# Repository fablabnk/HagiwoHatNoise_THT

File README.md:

# HagiwoHatNoise

# Notes

5v from Arduino or directly from 5V rail?
Patch submodule uses 22uF ceramic decoupling cap instead of 10uF electrolytic

# ToDo

- move decoupling caps close to Arduino on layout (both?!)

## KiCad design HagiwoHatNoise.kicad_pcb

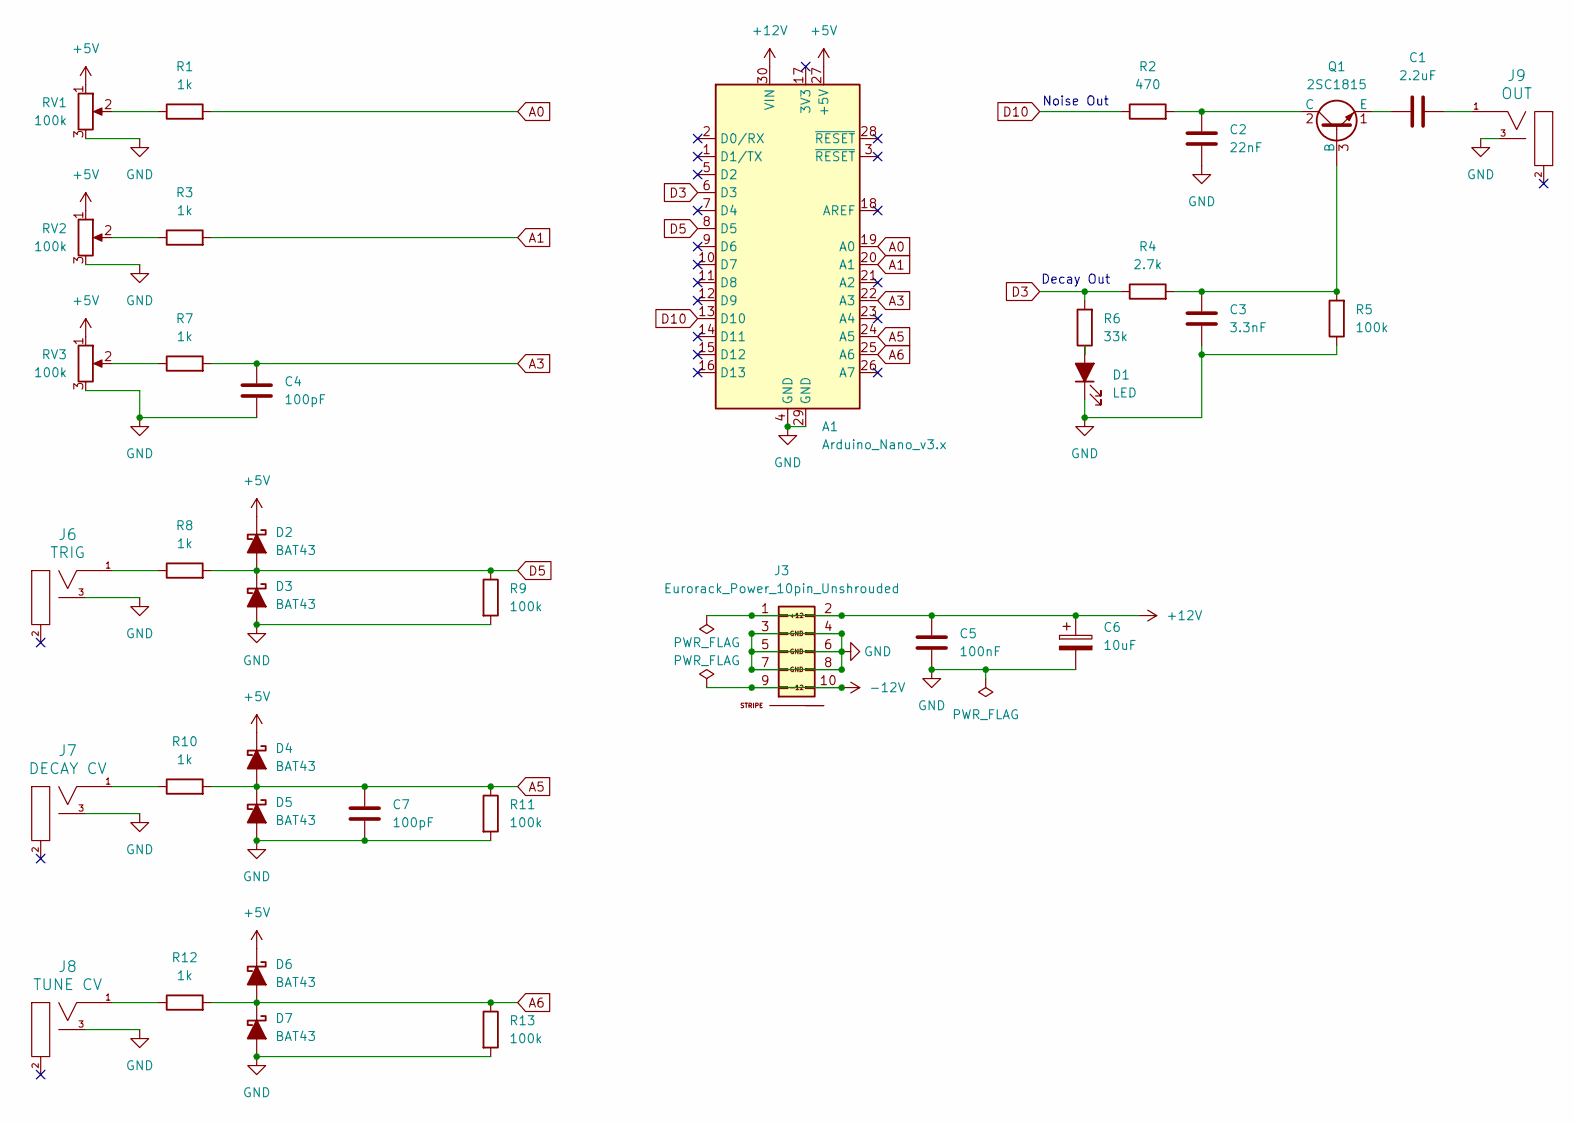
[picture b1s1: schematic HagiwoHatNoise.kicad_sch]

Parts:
A1: Arduino_Nano_v3.x; Arduino_Nano
C1: 2.2uF; C_Disc_D3.8mm_W2.6mm_P2.50mm
C2: 22nF; C_Disc_D3.8mm_W2.6mm_P2.50mm
C3: 3.3nF; C_Disc_D3.8mm_W2.6mm_P2.50mm
C4, C7: 100pF; C_Disc_D3.8mm_W2.6mm_P2.50mm
C5: 100nF; C_Disc_D3.8mm_W2.6mm_P2.50mm
C6: 10uF; CP_Radial_D4.0mm_P1.50mm
D1: LED; LED_D5.0mm
D2, D3, D4, D5, D6, D7: BAT43; D_DO-35_SOD27_P7.62mm_Horizontal_Widened_No_K
J3: Eurorack_Power_10pin_Unshrouded; IDC-Header_2x05_P2.54mm_Vertical_Euro_Power_Striped_Thicker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; Part Number 1-1002FBV0T
J6: TRIG; EighthInch_PJ398SM_3mmNPTH; Part Number WQP-WQP518MA
J7: DECAY CV; EighthInch_PJ398SM_3mmNPTH; Part Number WQP-WQP518MA
J8: TUNE CV; EighthInch_PJ398SM_3mmNPTH; Part Number WQP-WQP518MA
J9: OUT; EighthInch_PJ398SM_3mmNPTH; Part Number WQP-WQP518MA
Q1: 2SC1815; TO-92_Inline
R1, R3, R7, R8, R10, R12: 1k; R_Axial_DIN0207_L6.3mm_D2.5mm_P7.62mm_Horizontal
R2: 470; R_Axial_DIN0207_L6.3mm_D2.5mm_P7.62mm_Horizontal
R4: 2.7k; R_Axial_DIN0207_L6.3mm_D2.5mm_P7.62mm_Horizontal
R5, R9, R11, R13: 100k; R_Axial_DIN0207_L6.3mm_D2.5mm_P7.62mm_Horizontal
R6: 33k; R_Axial_DIN0207_L6.3mm_D2.5mm_P7.62mm_Horizontal
RV1, RV2, RV3: 100k; Pot_9mm_DShaft_RemovedPins4_5

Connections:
+5V: A1.27 (+5V), D2.1 (K), D4.1 (K), D6.1 (K), RV1.1, RV2.1, RV3.1
+12V: A1.30 (VIN), C5.1, C6.1, J3.1 (+12V), J3.2 (+12V)
-12V: J3.9 (-12V), J3.10 (-12V)
A0: A1.19 (A0), R1.2
A1: A1.20 (A1), R3.2
A3: A1.22 (A3), C4.1, R7.2
A5: A1.24 (A5), C7.1, D4.2 (A), D5.1 (K), R10.2, R11.1
A6: A1.25 (A6), D6.2 (A), D7.1 (K), R12.2, R13.1
D3: A1.6 (D3), R4.1, R6.2
D5: A1.8 (D5), D2.2 (A), D3.1 (K), R8.2, R9.1
D10: A1.13 (D10), R2.1
GND: A1.4 (GND), A1.29 (GND), C2.2, C3.2, C4.2, C5.2, C6.2, C7.2, D1.1 (K), D3.2 (A), D5.2 (A), D7.2 (A), J3.3 (GND), J3.4 (GND), J3.5 (GND), J3.6 (GND), J3.7 (GND), J3.8 (GND), J6.3 (SW), J7.3 (SW), J8.3 (SW), J9.3 (SW), R5.1, R9.2, R11.2, R13.2, RV1.3, RV2.3, RV3.3
unnamed: D1.2 (A), R6.1
unnamed: J6.1 (SIG), R8.1
unnamed: J7.1 (SIG), R10.1
unnamed: J8.1 (SIG), R12.1
unnamed: C1.2, J9.1 (SIG)
unnamed: C3.1, Q1.3 (B), R4.2, R5.2
unnamed: C2.1, Q1.2 (C), R2.2
unnamed: C1.1, Q1.1 (E)
unnamed: R1.1, RV1.2
unnamed: R3.1, RV2.2
unnamed: R7.1, RV3.2

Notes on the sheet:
Noise Out
Decay Out

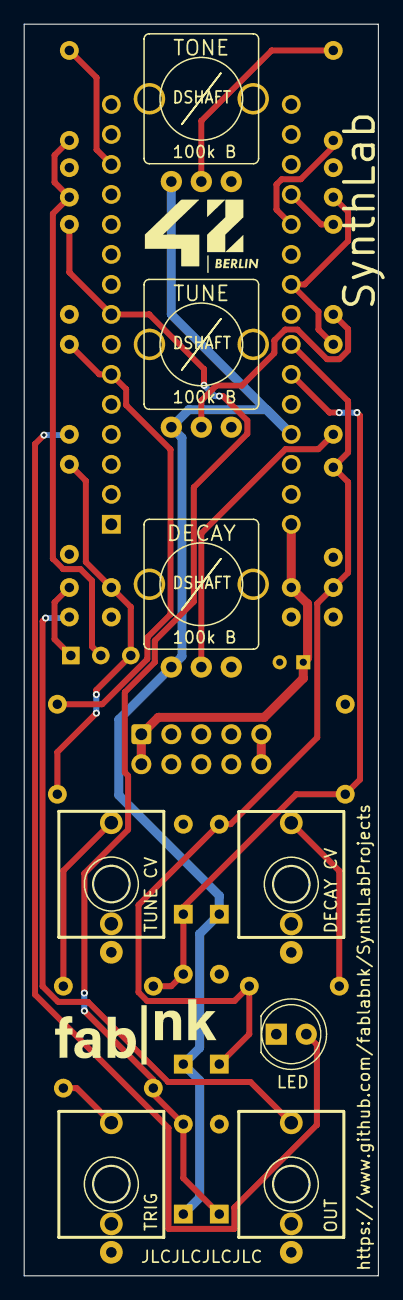
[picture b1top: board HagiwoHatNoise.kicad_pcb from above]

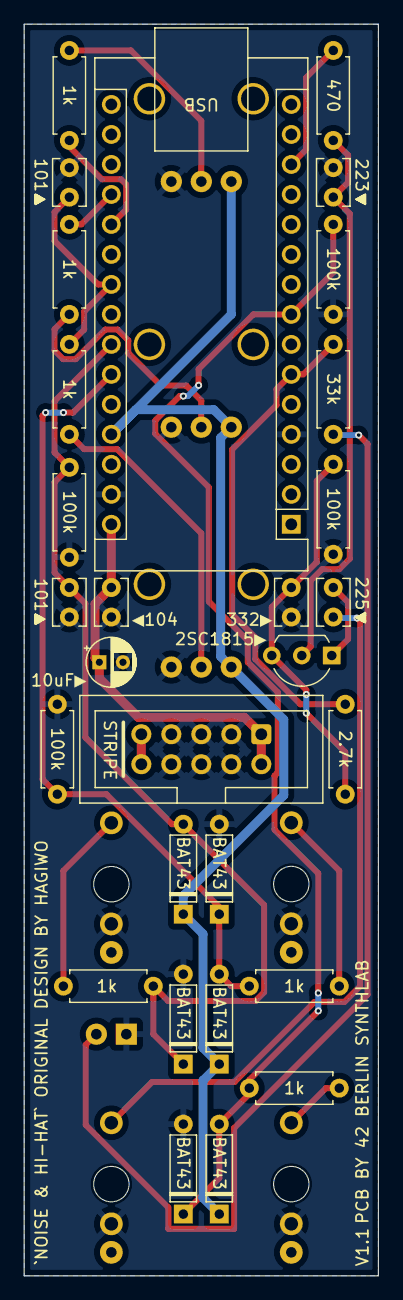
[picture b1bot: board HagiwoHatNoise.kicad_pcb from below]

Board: 2 copper layers, 30.0 x 106.0 mm, 37 parts (29 on the bottom side), 23 nets.

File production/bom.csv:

Designator,Footprint,Quantity,Value,LCSC Part #
A1,Arduino_Nano,1,Arduino_Nano_v3.x,
C1,C_Disc_D3.8mm_W2.6mm_P2.50mm,1,2.2uF,
C2,C_Disc_D3.8mm_W2.6mm_P2.50mm,1,22nF,
C3,C_Disc_D3.8mm_W2.6mm_P2.50mm,1,3.3nF,
"C4, C7",C_Disc_D3.8mm_W2.6mm_P2.50mm,2,100pF,
C5,C_Disc_D3.8mm_W2.6mm_P2.50mm,1,100nF,
C6,CP_Radial_D4.0mm_P1.50mm,1,10uF,
D1,LED_D5.0mm,1,LED,
"D2, D3, D4, D5, D6, D7",D_DO-35_SOD27_P7.62mm_Horizontal_Widened_No_K,6,BAT43,
J3,IDC-Header_2x05_P2.54mm_Vertical_Euro_Power_Striped_ThickerText,1,Eurorack_Power_10pin_Unshrouded,
J6,EighthInch_PJ398SM_3mmNPTH,1,TRIG,
J7,EighthInch_PJ398SM_3mmNPTH,1,DECAY CV,
J8,EighthInch_PJ398SM_3mmNPTH,1,TUNE CV,
J9,EighthInch_PJ398SM_3mmNPTH,1,OUT,
Q1,TO-92_Inline,1,2SC1815,
"R1, R10, R12, R3, R7, R8",R_Axial_DIN0207_L6.3mm_D2.5mm_P7.62mm_Horizontal,6,1k,
"R11, R13, R5, R9",R_Axial_DIN0207_L6.3mm_D2.5mm_P7.62mm_Horizontal,4,100k,
R2,R_Axial_DIN0207_L6.3mm_D2.5mm_P7.62mm_Horizontal,1,470,
R4,R_Axial_DIN0207_L6.3mm_D2.5mm_P7.62mm_Horizontal,1,2.7k,
R6,R_Axial_DIN0207_L6.3mm_D2.5mm_P7.62mm_Horizontal,1,33k,
"RV1, RV2, RV3",Pot_9mm_DShaft_RemovedPins4_5,3,100k,

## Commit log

2024-08-11 v1.0 ready for production
2024-08-13 latest updates
2024-09-15 added BuildNotes.md. Removed production folder
2024-09-15 Updated build notes
2024-09-22 v1.1 ready for final check
2024-09-25 v1.1 checked
2024-12-01 updating after Dmitri's changes
2024-12-14 added modified version of code which inverts pots to correct for miswiring of pins 1 and 3
